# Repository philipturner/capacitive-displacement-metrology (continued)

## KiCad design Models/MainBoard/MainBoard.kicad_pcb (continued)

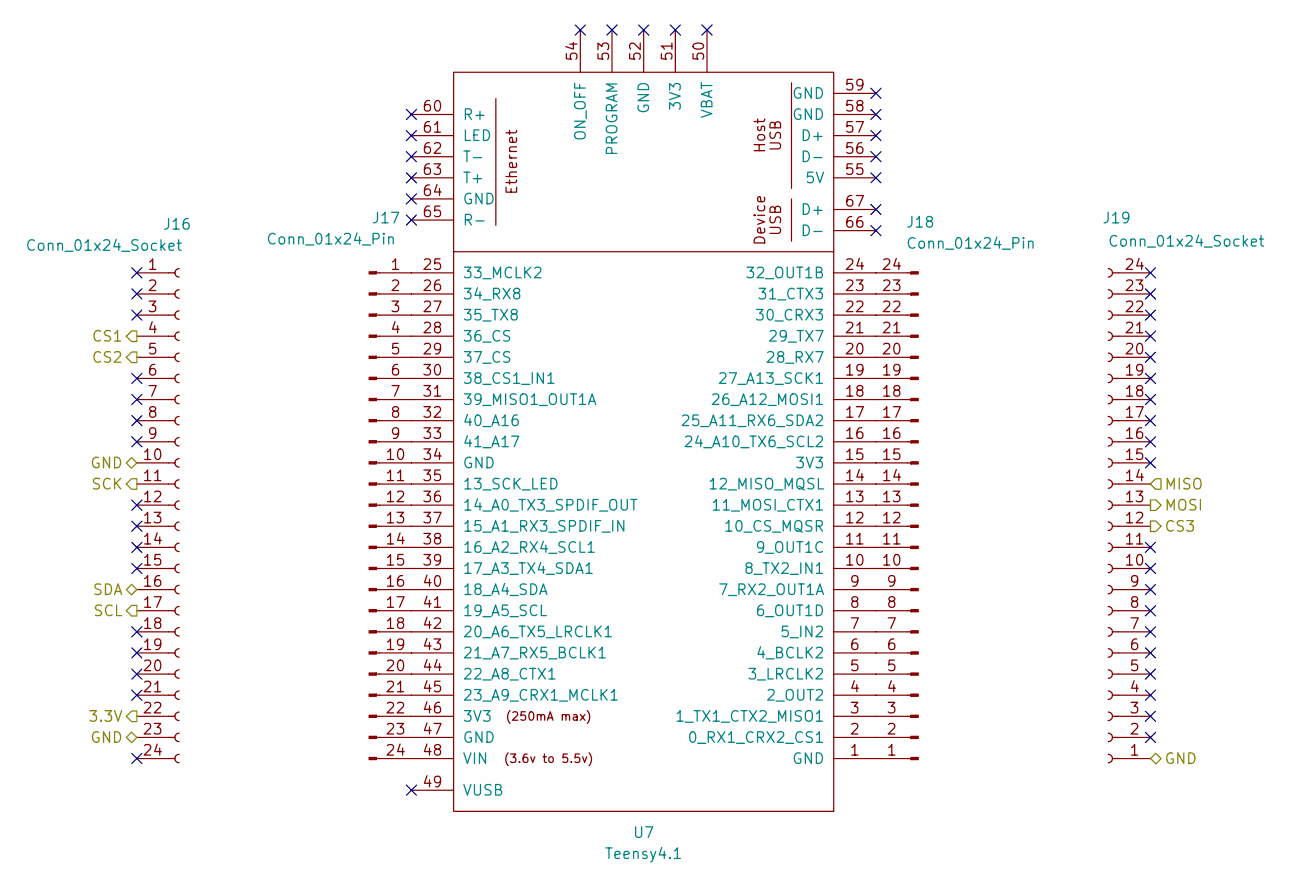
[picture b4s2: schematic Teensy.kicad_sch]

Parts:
J16, J19: Conn_01x24_Socket; PinSocket_1x24
J17, J18: Conn_01x24_Pin
U7: Teensy4.1

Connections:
/Isolation/3.3V_Digital: J16.22; also elsewhere on the board
/Isolation/CS1_Digital: J16.4; also elsewhere on the board
/Isolation/CS2_Digital: J16.5; also elsewhere on the board
/Isolation/CS3_Digital: J19.12; also elsewhere on the board
/Isolation/GND_Digital: J16.10, J16.23, J19.1; also elsewhere on the board
/Isolation/MISO_Digital: J19.14; also elsewhere on the board
/Isolation/MOSI_Digital: J19.13; also elsewhere on the board
/Isolation/SCK_Digital: J16.11; also elsewhere on the board
/Isolation/SCL_Digital: J16.17; also elsewhere on the board
/Isolation/SDA_Digital: J16.16; also elsewhere on the board
unnamed: J17.1, U7.25 (33_MCLK2)
unnamed: J17.2, U7.26 (34_RX8)
unnamed: J17.3, U7.27 (35_TX8)
unnamed: J17.4, U7.28 (36_CS)
unnamed: J17.5, U7.29 (37_CS)
unnamed: J17.6, U7.30 (38_CS1_IN1)
unnamed: J17.7, U7.31 (39_MISO1_OUT1A)
unnamed: J17.8, U7.32 (40_A16)
unnamed: J17.9, U7.33 (41_A17)
unnamed: J17.10, U7.34 (GND)
unnamed: J17.11, U7.35 (13_SCK_LED)
unnamed: J17.12, U7.36 (14_A0_TX3_SPDIF_OUT)
unnamed: J17.13, U7.37 (15_A1_RX3_SPDIF_IN)
unnamed: J17.14, U7.38 (16_A2_RX4_SCL1)
unnamed: J17.15, U7.39 (17_A3_TX4_SDA1)
unnamed: J17.16, U7.40 (18_A4_SDA)
unnamed: J17.17, U7.41 (19_A5_SCL)
unnamed: J17.18, U7.42 (20_A6_TX5_LRCLK1)
unnamed: J17.19, U7.43 (21_A7_RX5_BCLK1)
unnamed: J17.20, U7.44 (22_A8_CTX1)
unnamed: J17.21, U7.45 (23_A9_CRX1_MCLK1)
unnamed: J17.22, U7.46 (3V3)
unnamed: J17.23, U7.47 (GND)
unnamed: J17.24, U7.48 (VIN)
unnamed: J18.1, U7.1 (GND)
unnamed: J18.2, U7.2 (0_RX1_CRX2_CS1)
unnamed: J18.3, U7.3 (1_TX1_CTX2_MISO1)
unnamed: J18.4, U7.4 (2_OUT2)
unnamed: J18.5, U7.5 (3_LRCLK2)
unnamed: J18.6, U7.6 (4_BCLK2)
unnamed: J18.7, U7.7 (5_IN2)
unnamed: J18.8, U7.8 (6_OUT1D)
unnamed: J18.9, U7.9 (7_RX2_OUT1A)
unnamed: J18.10, U7.10 (8_TX2_IN1)
unnamed: J18.11, U7.11 (9_OUT1C)
unnamed: J18.12, U7.12 (10_CS_MQSR)
unnamed: J18.13, U7.13 (11_MOSI_CTX1)
unnamed: J18.14, U7.14 (12_MISO_MQSL)
unnamed: J18.15, U7.15 (3V3)
unnamed: J18.16, U7.16 (24_A10_TX6_SCL2)
unnamed: J18.17, U7.17 (25_A11_RX6_SDA2)
unnamed: J18.18, U7.18 (26_A12_MOSI1)
unnamed: J18.19, U7.19 (27_A13_SCK1)
unnamed: J18.20, U7.20 (28_RX7)
unnamed: J18.21, U7.21 (29_TX7)
unnamed: J18.22, U7.22 (30_CRX3)
unnamed: J18.23, U7.23 (31_CTX3)
unnamed: J18.24, U7.24 (32_OUT1B)

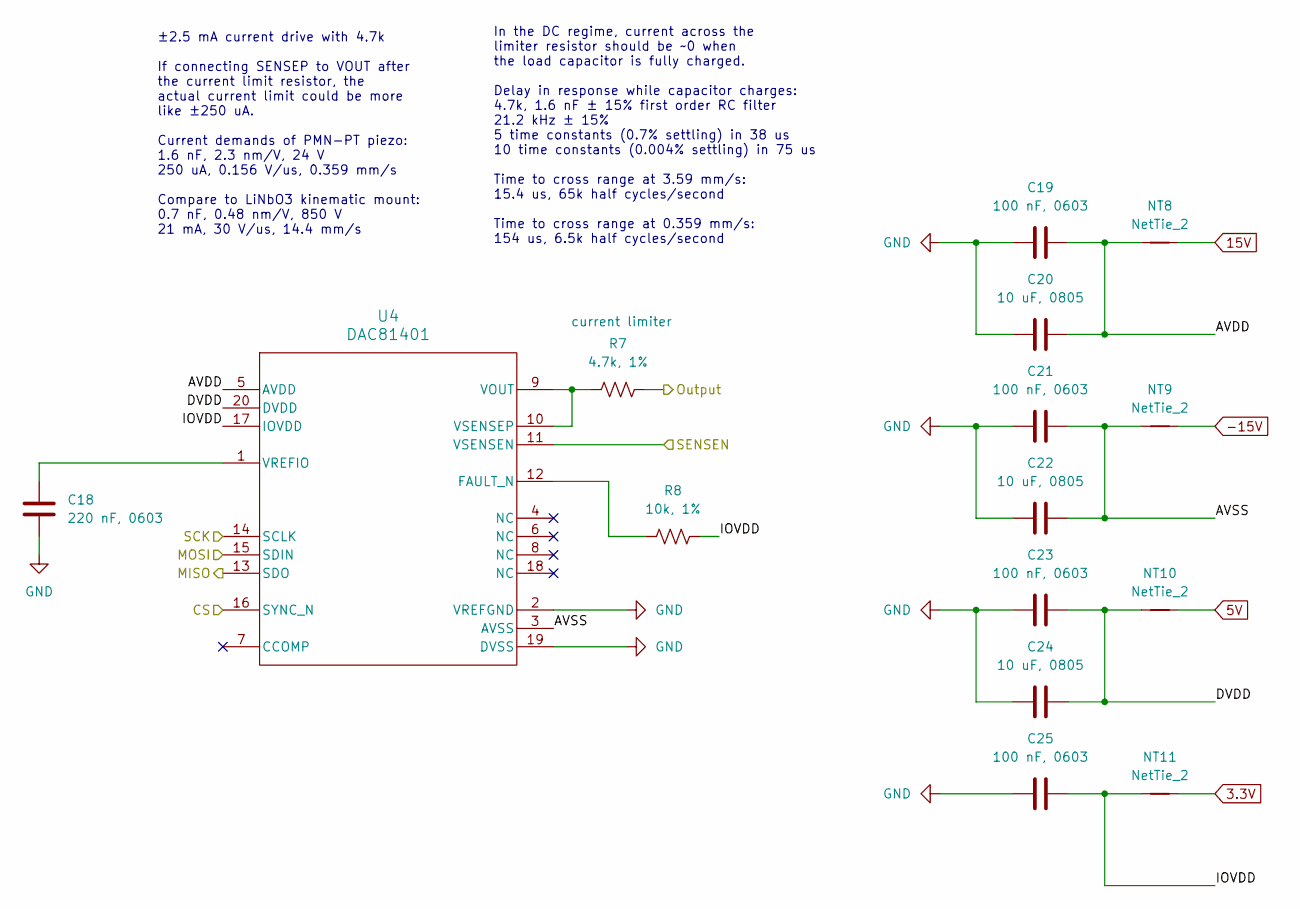
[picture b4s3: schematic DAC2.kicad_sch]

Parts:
C18: 220 nF, 0603; CAPC0603
C19, C21, C23, C25: 100 nF, 0603; CAPC0603
C20, C22, C24: 10 uF, 0805; CAPC0805
NT8, NT9, NT10, NT11: NetTie_2; NetTie_0.15mm
R7: 4.7k, 1%; RESC0603
R8: 10k, 1%; RESC0603
U4: DAC81401; TSSOP-20

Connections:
3.3V: NT11.2; also elsewhere on the board
5V: NT10.2; also elsewhere on the board
15V: NT8.2; also elsewhere on the board
-15V: NT9.2; also elsewhere on the board
/ADC/MISO: U4.13 (SDO); also elsewhere on the board
/ADC/MOSI: U4.15 (SDIN); also elsewhere on the board
/ADC/SCK: U4.14 (SCLK); also elsewhere on the board
/BIAS_GND: U4.11 (VSENSEN); also elsewhere on the board
/BIAS_OUT: R7.2; also elsewhere on the board
/CS2: U4.16 (SYNC_N); also elsewhere on the board
/DAC2/AVDD: C19.2, C20.2, NT8.1, U4.5 (AVDD)
/DAC2/AVSS: C21.2, C22.2, NT9.1, U4.3 (AVSS)
/DAC2/DVDD: C23.2, C24.2, NT10.1, U4.20 (DVDD)
/DAC2/IOVDD: C25.2, NT11.1, R8.2, U4.17 (IOVDD)
GND: C18.2, C19.1, C20.1, C21.1, C22.1, C23.1, C24.1, C25.1, U4.2 (VREFGND), U4.19 (DVSS); also elsewhere on the board
unnamed: R8.1, U4.12 (FAULT_N)
unnamed: R7.1, U4.9 (VOUT), U4.10 (VSENSEP)
unnamed: C18.1, U4.1 (VREFIO)

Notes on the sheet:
±2.5 mA current drive with 4.7k If connecting SENSEP to VOUT after the current limit resistor, the actual current limit could be more like ±250 uA. Current demands of PMN-PT piezo: 1.6 nF, 2.3 nm/V, 24 V 250 uA, 0.156 V/us, 0.359 mm/s Compare to LiNbO3 kinematic mount: 0.7 nF, 0.48 nm/V, 850 V 21 m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
In the DC regime, current across the limiter resistor should be ~0 when the load capacitor is fully charged. Delay in response while capacitor charges: 4.7k, 1.6 nF ± 15% first order RC filter 21.2 kHz ± 15% 5 time constants (0.7% settling) in 38 us 10 time constants (0.004% settling) in 75 us Time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

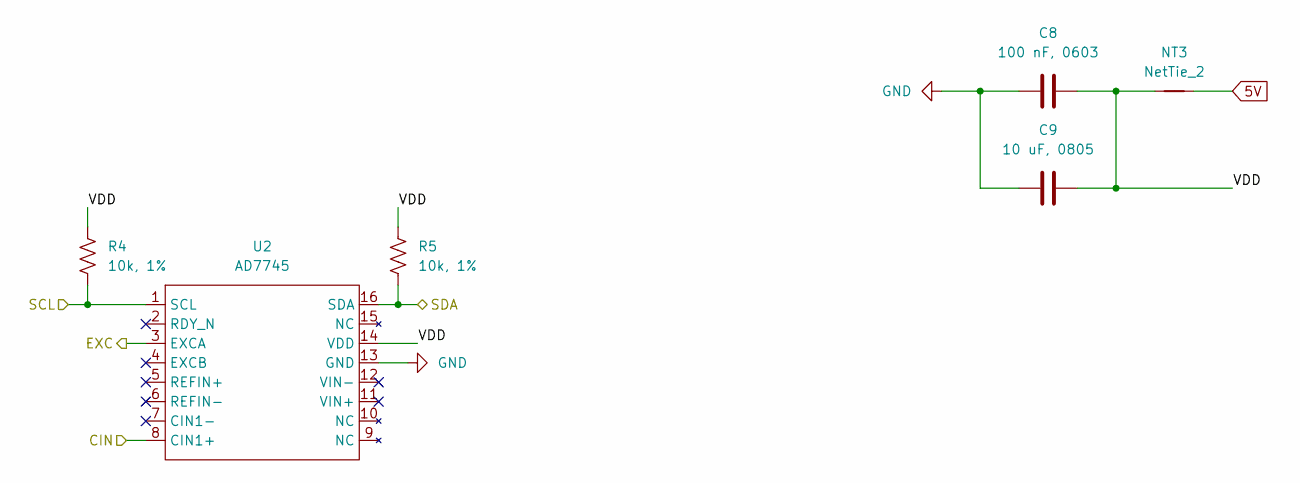
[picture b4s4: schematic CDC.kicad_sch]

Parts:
C8: 100 nF, 0603; CAPC0603
C9: 10 uF, 0805; CAPC0805
NT3: NetTie_2; NetTie_0.15mm
R4, R5: 10k, 1%; RESC0603
U2: AD7745; TSSOP-16

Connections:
5V: NT3.2; also elsewhere on the board
/CDC/SCL: R4.2, U2.1 (SCL); also elsewhere on the board
/CDC/SDA: R5.2, U2.16 (SDA); also elsewhere on the board
/CDC/VDD: C8.2, C9.2, NT3.1, R4.1, R5.1, U2.14 (VDD)
/CDC_CIN: U2.8 (CIN1+); also elsewhere on the board
/CDC_EXC: U2.3 (EXCA); also elsewhere on the board
GND: C8.1, C9.1, U2.13 (GND); also elsewhere on the board

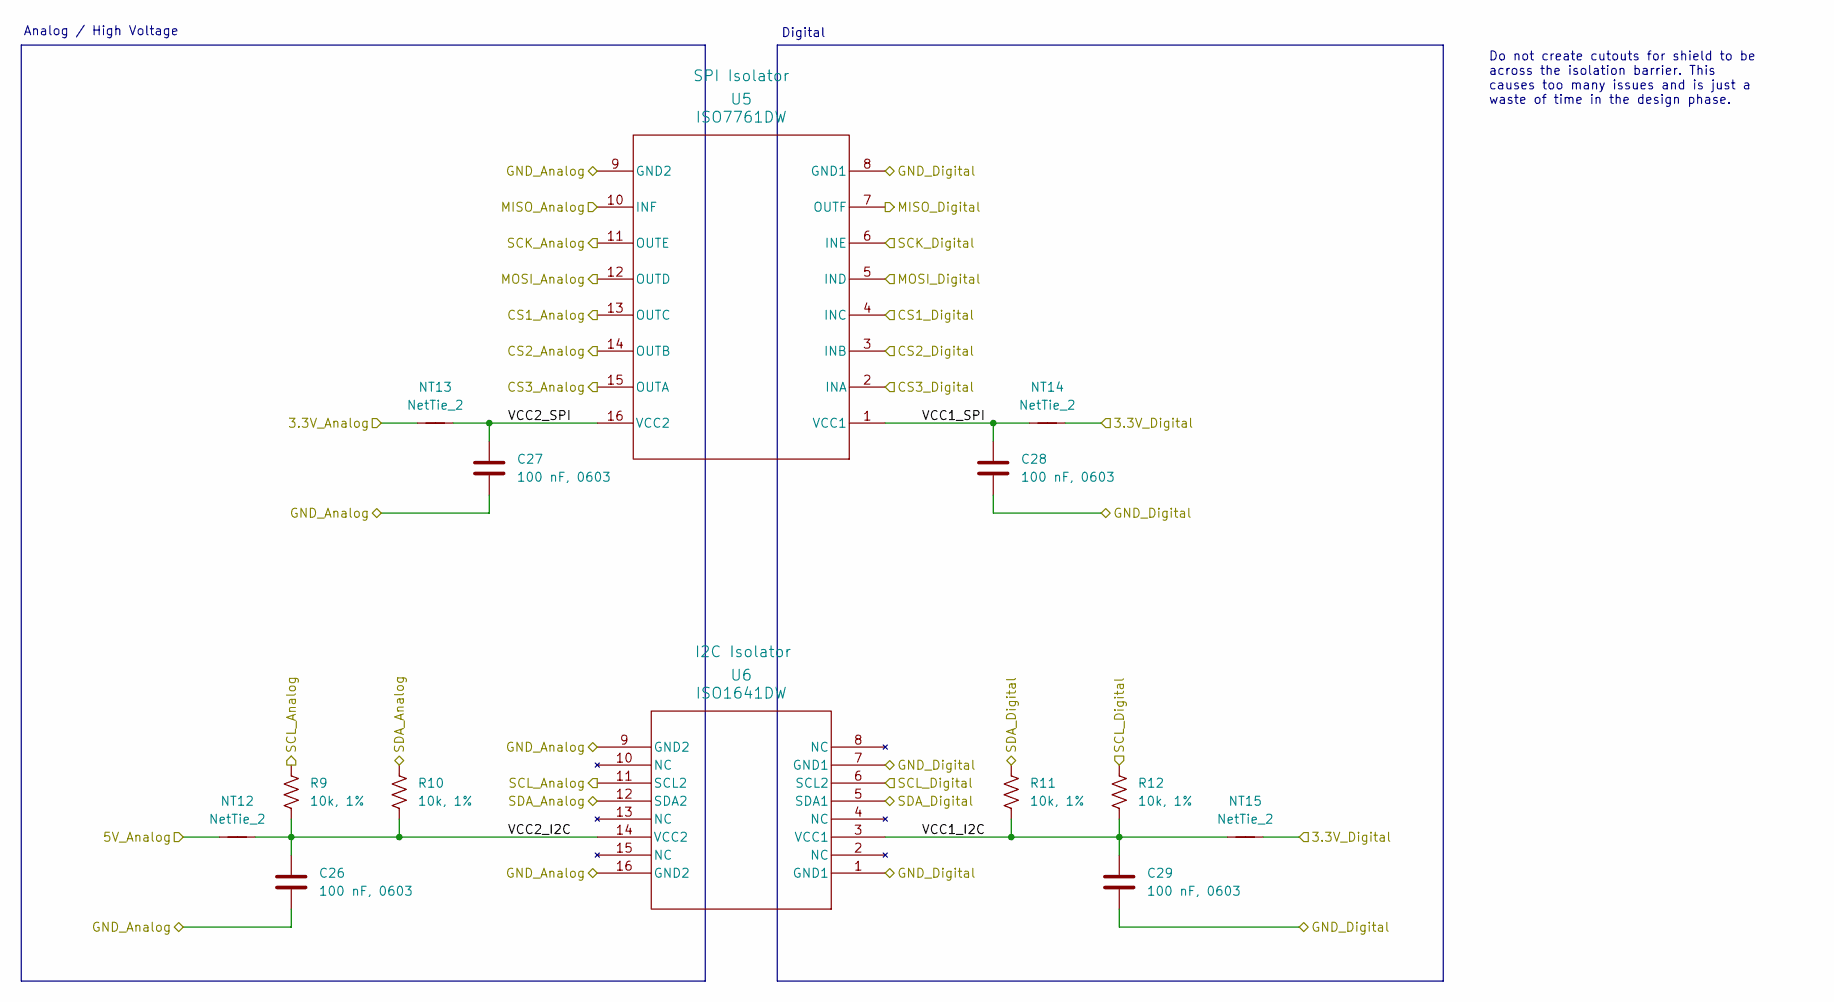
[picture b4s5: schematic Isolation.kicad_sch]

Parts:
C26, C27, C28, C29: 100 nF, 0603; CAPC0603
NT12, NT13, NT14, NT15: NetTie_2; NetTie_0.15mm
R9, R10, R11, R12: 10k, 1%; RESC0603
U5: ISO7761DW; SOIC-16-Wide
U6: ISO1641DW; SOIC-16-Wide

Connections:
3.3V: NT13.1; also elsewhere on the board
5V: NT12.1; also elsewhere on the board
/ADC/MISO: U5.10 (INF); also elsewhere on the board
/ADC/MOSI: U5.12 (OUTD); also elsewhere on the board
/ADC/SCK: U5.11 (OUTE); also elsewhere on the board
/CDC/SCL: R9.1, U6.11 (SCL2); also elsewhere on the board
/CDC/SDA: R10.1, U6.12 (SDA2); also elsewhere on the board
/CS1: U5.13 (OUTC); also elsewhere on the board
/CS2: U5.14 (OUTB); also elsewhere on the board
/CS3: U5.15 (OUTA); also elsewhere on the board
/Isolation/3.3V_Digital: NT14.2, NT15.2; also elsewhere on the board
/Isolation/CS1_Digital: U5.4 (INC); also elsewhere on the board
/Isolation/CS2_Digital: U5.3 (INB); also elsewhere on the board
/Isolation/CS3_Digital: U5.2 (INA); also elsewhere on the board
/Isolation/GND_Digital: C28.2, C29.2, U5.8 (GND1), U6.1 (GND1), U6.7 (GND1); also elsewhere on the board
/Isolation/MISO_Digital: U5.7 (OUTF); also elsewhere on the board
/Isolation/MOSI_Digital: U5.5 (IND); also elsewhere on the board
/Isolation/SCK_Digital: U5.6 (INE); also elsewhere on the board
/Isolation/SCL_Digital: R12.1, U6.6 (SCL2); also elsewhere on the board
/Isolation/SDA_Digital: R11.1, U6.5 (SDA1); also elsewhere on the board
/Isolation/VCC1_I2C: C29.1, NT15.1, R11.2, R12.2, U6.3 (VCC1)
/Isolation/VCC1_SPI: C28.1, NT14.1, U5.1 (VCC1)
/Isolation/VCC2_I2C: C26.1, NT12.2, R9.2, R10.2, U6.14 (VCC2)
/Isolation/VCC2_SPI: C27.1, NT13.2, U5.16 (VCC2)
GND: C26.2, C27.2, U5.9 (GND2), U6.9 (GND2), U6.16 (GND2); also elsewhere on the board

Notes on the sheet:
Do not create cutouts for shield to be across the isolation barrier. This causes too many issues and is just a waste of time in the design phase.
Analog / High Voltage
Digital

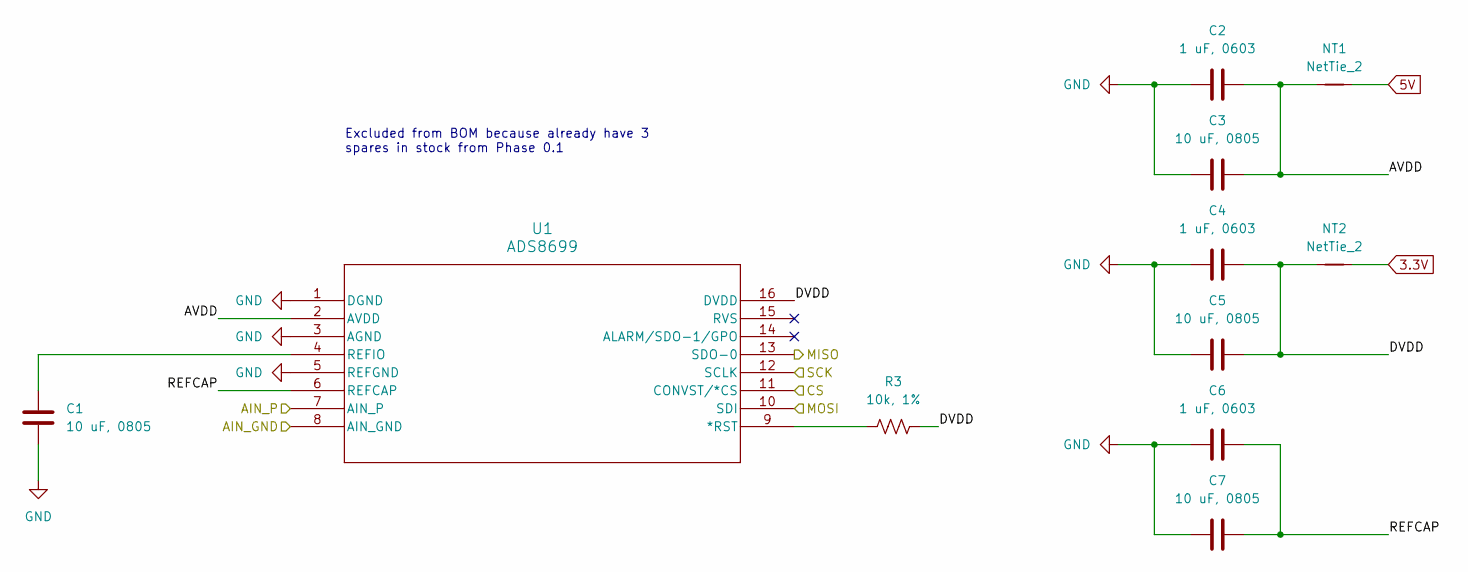
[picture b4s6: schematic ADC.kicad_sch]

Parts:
C1, C3, C5, C7: 10 uF, 0805; CAPC0805
C2, C4, C6: 1 uF, 0603; CAPC0603
NT1, NT2: NetTie_2; NetTie_0.15mm
R3: 10k, 1%; RESC0603
U1: ADS8699; TSSOP-16

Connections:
3.3V: NT2.2; also elsewhere on the board
5V: NT1.2; also elsewhere on the board
/ADC/AVDD: C2.2, C3.2, NT1.1, U1.2 (AVDD)
/ADC/DVDD: C4.2, C5.2, NT2.1, R3.2, U1.16 (DVDD)
/ADC/MISO: U1.13 (SDO-0); also elsewhere on the board
/ADC/MOSI: U1.10 (SDI); also elsewhere on the board
/ADC/REFCAP: C6.2, C7.2, U1.6 (REFCAP)
/ADC/SCK: U1.12 (SCLK); also elsewhere on the board
/ADC_GND: U1.8 (AIN_GND); also elsewhere on the board
/ADC_IN: U1.7 (AIN_P); also elsewhere on the board
/CS3: U1.11 (CONVST/*CS); also elsewhere on the board
GND: C1.2, C2.1, C3.1, C4.1, C5.1, C6.1, C7.1, U1.1 (DGND), U1.3 (AGND), U1.5 (REFGND); also elsewhere on the board
unnamed: R3.1, U1.9 (*RST)
unnamed: C1.1, U1.4 (REFIO)

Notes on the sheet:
Excluded from BOM because already have 3 spares in stock from Phase 0.1

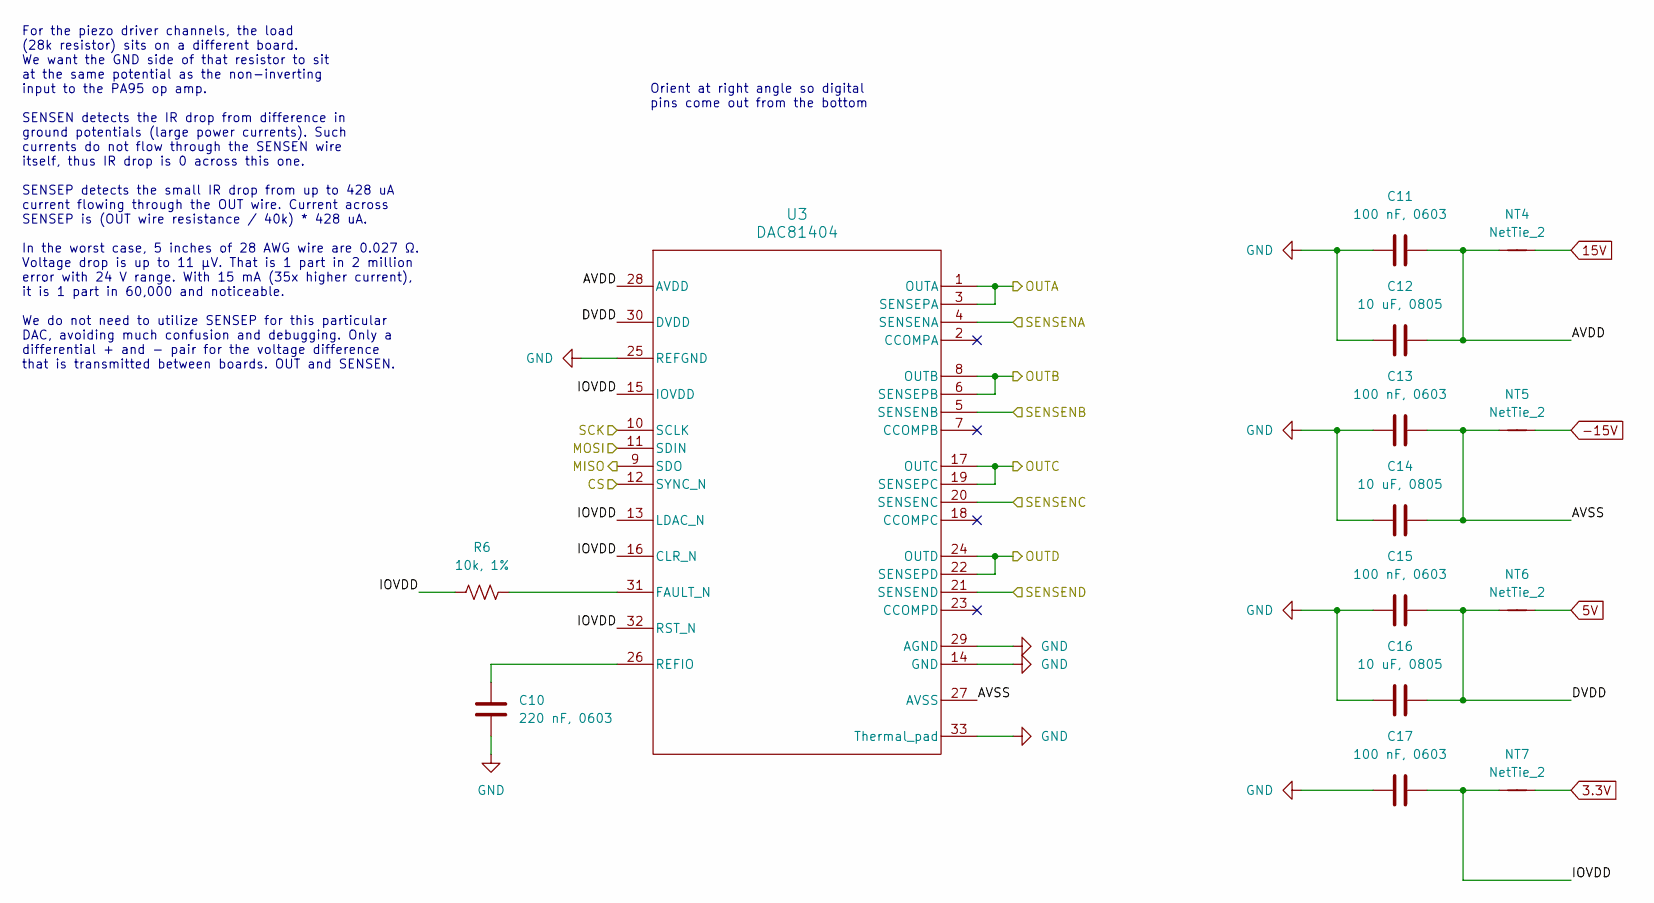
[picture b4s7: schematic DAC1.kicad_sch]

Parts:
C10: 220 nF, 0603; CAPC0603
C11, C13, C15, C17: 100 nF, 0603; CAPC0603
C12, C14, C16: 10 uF, 0805; CAPC0805
NT4, NT5, NT6, NT7: NetTie_2; NetTie_0.15mm
R6: 10k, 1%; RESC0603
U3: DAC81404; VQFN-32

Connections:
3.3V: NT7.2; also elsewhere on the board
5V: NT6.2; also elsewhere on the board
15V: NT4.2; also elsewhere on the board
-15V: NT5.2; also elsewhere on the board
/ADC/MISO: U3.9 (SDO); also elsewhere on the board
/ADC/MOSI: U3.11 (SDIN); also elsewhere on the board
/ADC/SCK: U3.10 (SCLK); also elsewhere on the board
/CS1: U3.12 (SYNC_N); also elsewhere on the board
/DAC1/AVDD: C11.2, C12.2, NT4.1, U3.28 (AVDD)
/DAC1/AVSS: C13.2, C14.2, NT5.1, U3.27 (AVSS)
/DAC1/DVDD: C15.2, C16.2, NT6.1, U3.30 (DVDD)
/DAC1/IOVDD: C17.2, NT7.1, R6.1, U3.13 (LDAC_N), U3.15 (IOVDD), U3.16 (CLR_N), U3.32 (RST_N)
/OUTA: U3.1 (OUTA), U3.3 (SENSEPA); also elsewhere on the board
/OUTB: U3.6 (SENSEPB), U3.8 (OUTB); also elsewhere on the board
/OUTC: U3.17 (OUTC), U3.19 (SENSEPC); also elsewhere on the board
/OUTD: U3.22 (SENSEPD), U3.24 (OUTD); also elsewhere on the board
/SENSENA: U3.4 (SENSENA); also elsewhere on the board
/SENSENB: U3.5 (SENSENB); also elsewhere on the board
/SENSENC: U3.20 (SENSENC); also elsewhere on the board
/SENSEND: U3.21 (SENSEND); also elsewhere on the board
GND: C10.2, C11.1, C12.1, C13.1, C14.1, C15.1, C16.1, C17.1, U3.14 (GND), U3.25 (REFGND), U3.29 (AGND), U3.33 (Thermal_pad); also elsewhere on the board
unnamed: R6.2, U3.31 (FAULT_N)
unnamed: C10.1, U3.26 (REFIO)

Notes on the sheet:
Orient at right angle so digital pins come out from the bottom
For the piezo driver channels, the load (28k resistor) sits on a different board. We want the GND side of that resistor to sit at the same potential as the non-inverting input to the PA95 op amp. SENSEN detects the IR drop from difference in ground potentials (large power currents). Such currents d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

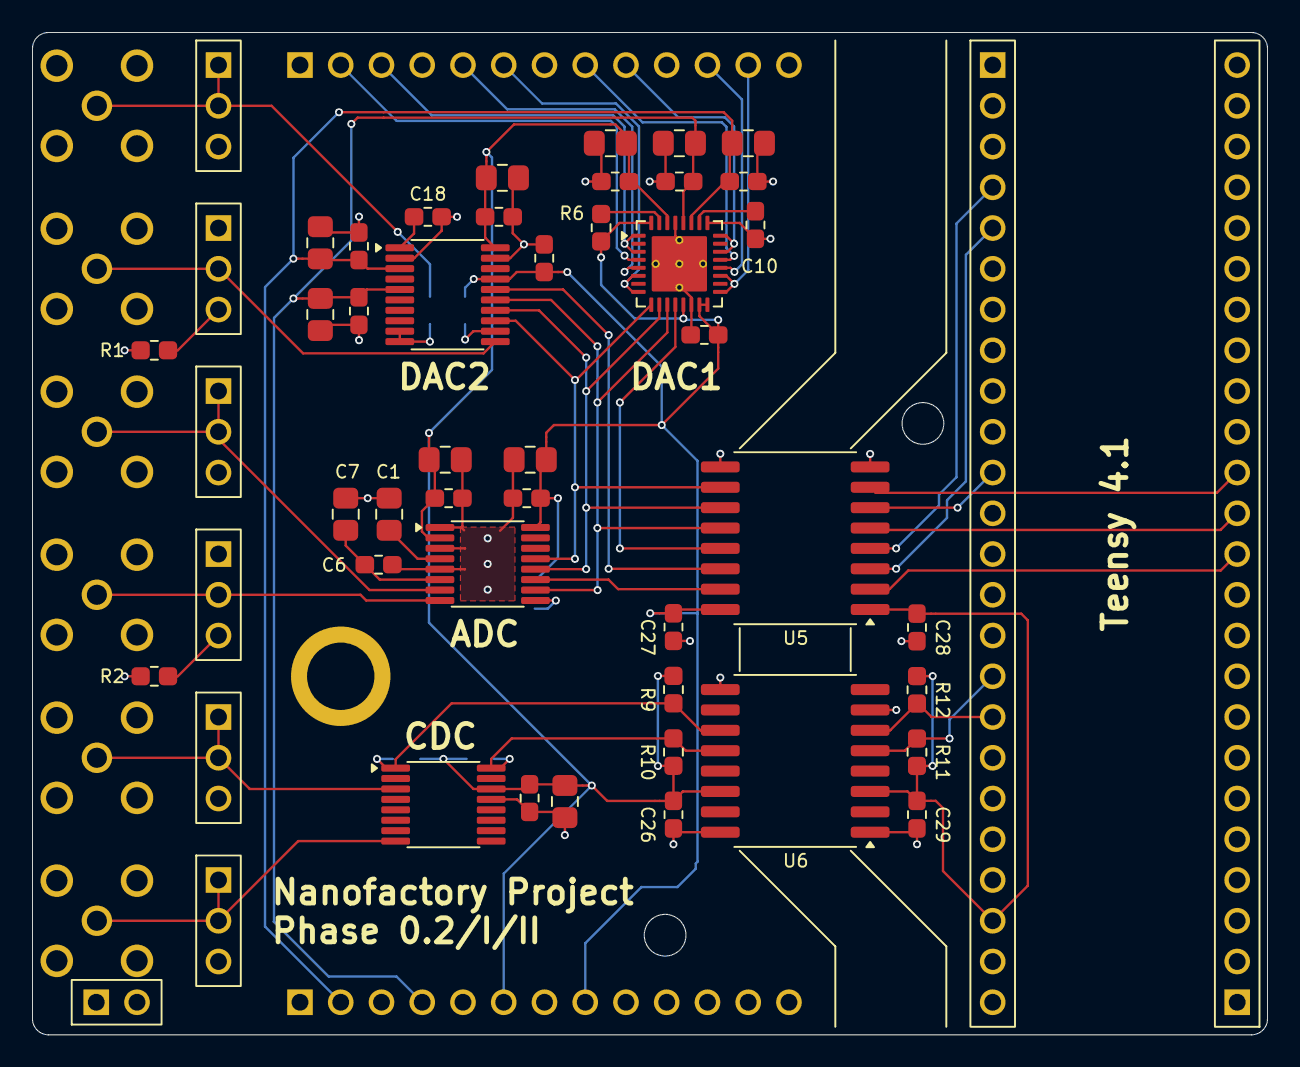
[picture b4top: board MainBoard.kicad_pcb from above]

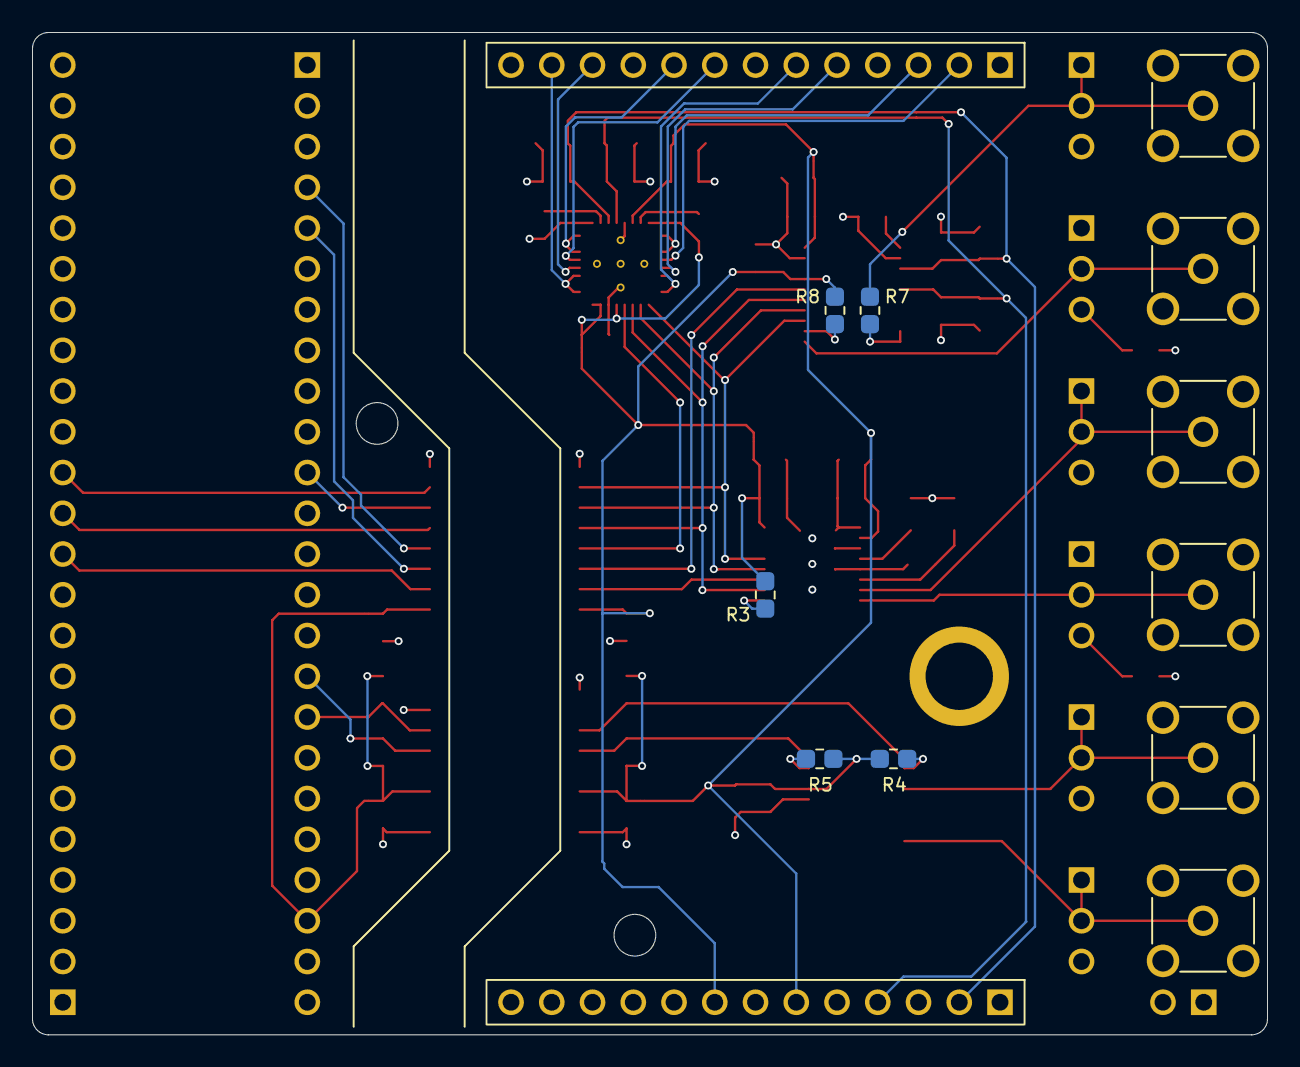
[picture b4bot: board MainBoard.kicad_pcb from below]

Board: 4 copper layers, 77.0 x 62.5 mm, 82 parts (13 on the bottom side), 62 nets.

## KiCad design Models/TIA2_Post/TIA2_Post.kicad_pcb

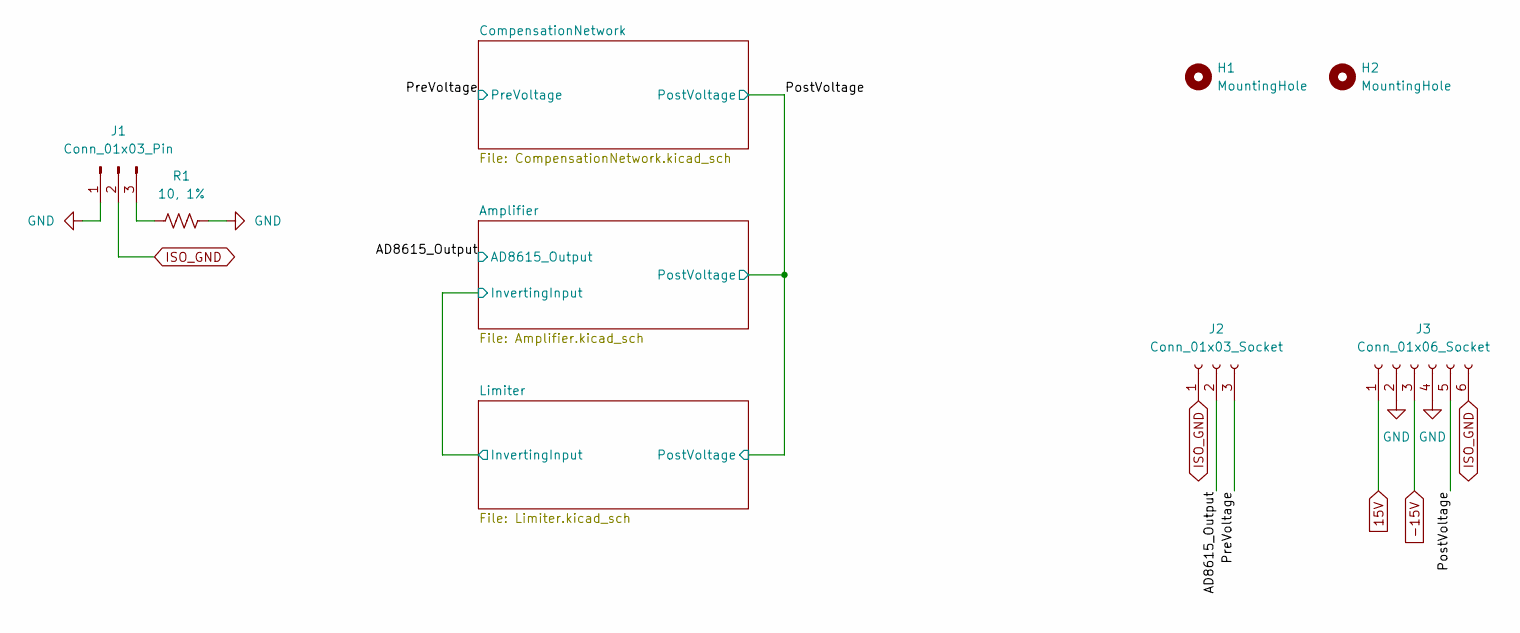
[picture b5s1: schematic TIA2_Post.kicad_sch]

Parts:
H1, H2: MountingHole; DowelPin_2.5mm
J1: Conn_01x03_Pin; PinHeader_1x3
J2: Conn_01x03_Socket; PinSocket_1x3
J3: Conn_01x06_Socket; PinSocket_1x6
R1: 10, 1%; RESC0603

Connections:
15V: J3.1; also elsewhere on the board
-15V: J3.3; also elsewhere on the board
/AD8615_Output: J2.2; also elsewhere on the board
/PostVoltage: J3.5; also elsewhere on the board
/PreVoltage: J2.3; also elsewhere on the board
GND: J1.1, J3.2, J3.4, R1.2; also elsewhere on the board
ISO_GND: J1.2, J2.1, J3.6; also elsewhere on the board
unnamed: J1.3, R1.1

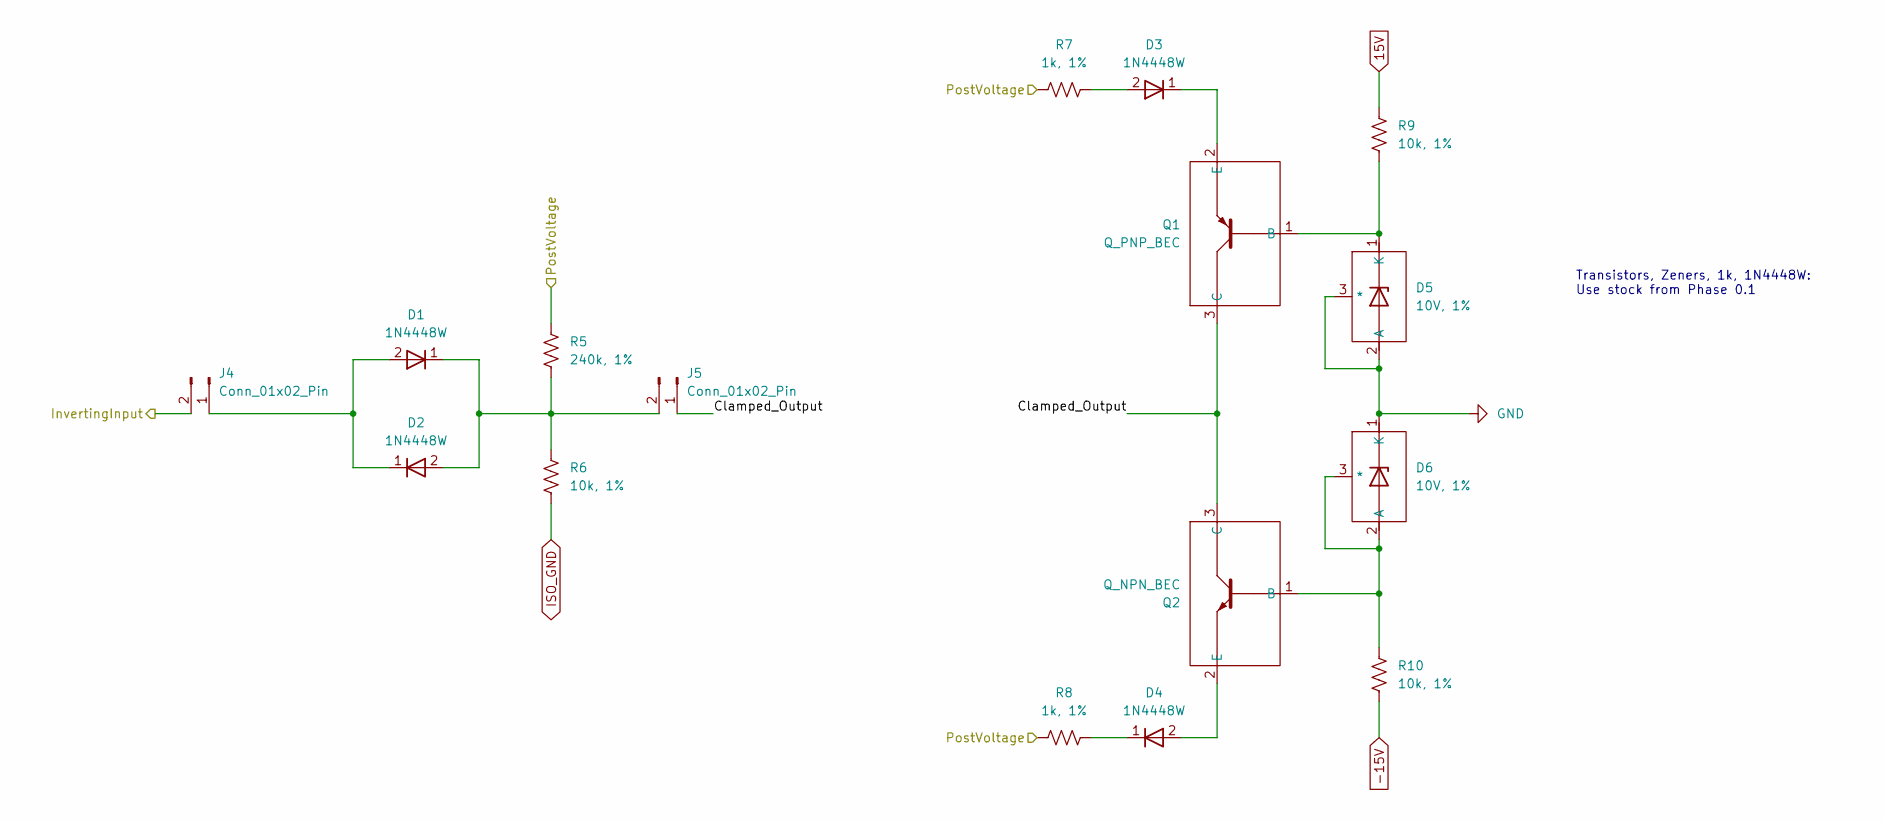
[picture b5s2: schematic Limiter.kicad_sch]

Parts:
D1, D2, D3, D4: 1N4448W; SOD-123
D5, D6: 10V, 1%; SOT-23
J4, J5: Conn_01x02_Pin; PinHeader_1x2
Q1: Q_PNP_BEC; SOT-23
Q2: Q_NPN_BEC; SOT-23
R5: 240k, 1%; RESC0603
R6, R9, R10: 10k, 1%; RESC0603
R7, R8: 1k, 1%; RESC0603

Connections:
15V: R9.1; also elsewhere on the board
-15V: R10.2; also elsewhere on the board
/Amplifier/InvertingInput: J4.2; also elsewhere on the board
/Limiter/Clamped_Output: J5.1, Q1.3 (C), Q2.3 (C)
/PostVoltage: R5.1, R7.1, R8.1; also elsewhere on the board
GND: D5.2 (A), D5.3 (*), D6.1 (K); also elsewhere on the board
ISO_GND: R6.2; also elsewhere on the board
unnamed: D1.2 (A), D2.1 (K), J4.1
unnamed: D1.1 (K), D2.2 (A), J5.2, R5.2, R6.1
unnamed: D3.2 (A), R7.2
unnamed: D3.1 (K), Q1.2 (E)
unnamed: D4.2 (A), Q2.2 (E)
unnamed: D4.1 (K), R8.2
unnamed: D5.1 (K), Q1.1 (B), R9.2
unnamed: D6.2 (A), D6.3 (*), Q2.1 (B), R10.1

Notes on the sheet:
Transistors, Zeners, 1k, 1N4448W: Use stock from Phase 0.1

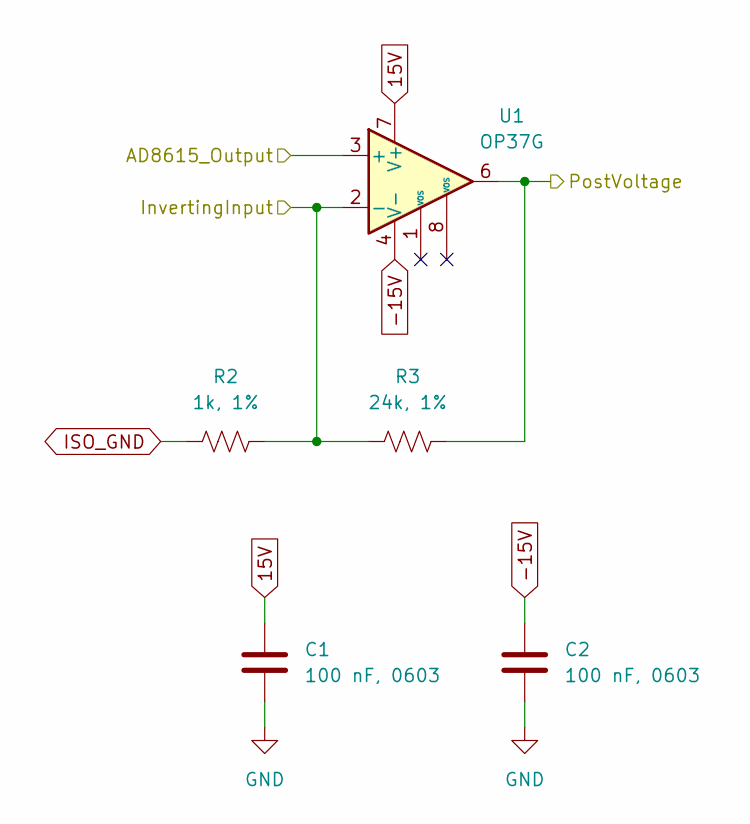
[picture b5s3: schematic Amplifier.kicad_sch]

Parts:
C1, C2: 100 nF, 0603; CAPC0603
R2: 1k, 1%; RESC0603
R3: 24k, 1%; RESC0603
U1: OP37G; SOIC-8

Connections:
15V: C1.1, U1.7 (V+); also elsewhere on the board
-15V: C2.1, U1.4 (V-); also elsewhere on the board
/AD8615_Output: U1.3 (+); also elsewhere on the board
/Amplifier/InvertingInput: R2.2, R3.1, U1.2 (-); also elsewhere on the board
/PostVoltage: R3.2, U1.6; also elsewhere on the board
GND: C1.2, C2.2; also elsewhere on the board
ISO_GND: R2.1; also elsewhere on the board

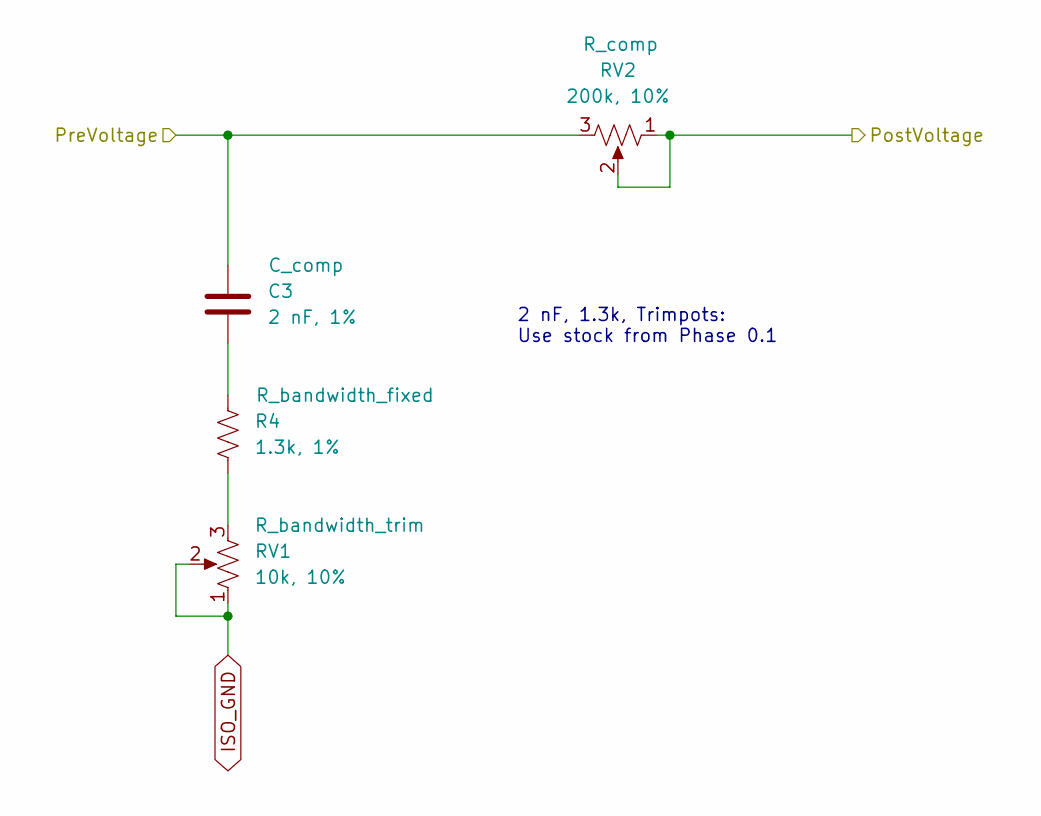
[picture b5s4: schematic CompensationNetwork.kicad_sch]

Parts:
C3: 2 nF, 1%; CAPC0603
R4: 1.3k, 1%; RESC0603
RV1: 10k, 10%; Bourns_3296Y
RV2: 200k, 10%; Bourns_3296Y

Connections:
/PostVoltage: RV2.1, RV2.2; also elsewhere on the board
/PreVoltage: C3.1, RV2.3; also elsewhere on the board
ISO_GND: RV1.1, RV1.2; also elsewhere on the board
unnamed: C3.2, R4.1
unnamed: R4.2, RV1.3

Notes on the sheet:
2 nF, 1.3k, Trimpots: Use stock from Phase 0.1

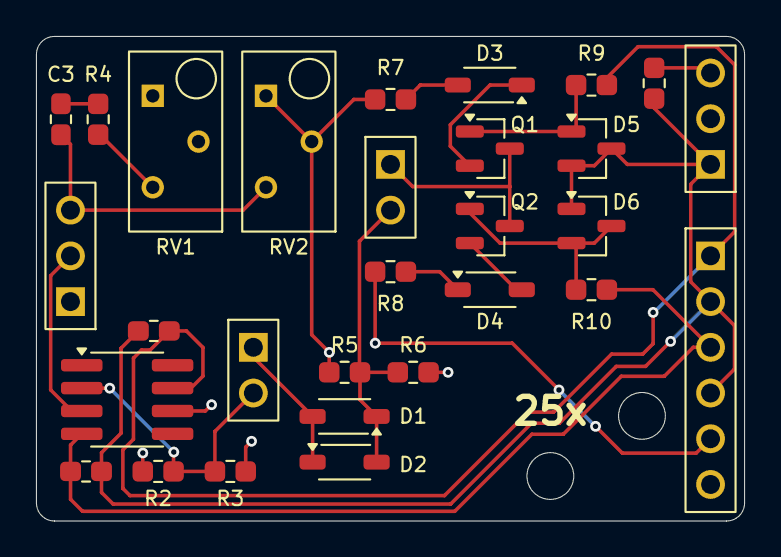
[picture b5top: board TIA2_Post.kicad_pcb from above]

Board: 2 copper layers, 39.3 x 26.9 mm, 31 parts (0 on the bottom side), 20 nets.
